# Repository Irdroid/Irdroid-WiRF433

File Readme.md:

#Irdroid WiRF433 - Single Board Linux Computer, Designed by Hardwate Group Ltd.
------------------------------------------------------------------------------
Irdroid WiRF433 is open source software and open source hardware, low cost starting
from USD 38 Linux Industrial grade single board computer with GPIOs capable to operate 
-25 - +85C

The Irdroid WiRF433 SBC is designed with the Ralink RT5350 SoC, 32Mbytes of RAM and 4 Mbytes of Flash.
The Irdroid WiRF433 board is designed with 2 ethernet ports, therefore the board can be 
used for routing. 

All the GPIOs of the RT5350 Soc are available on the WiRF433 board pin headers. The Irdroid WiRF433
comes also with a RF433MHZ RF module which allows for controlling IoT Remote control switches, light bulbs
and sockets operating at 433.9Mhz.

Irdroid WiRF433 is completely open source - including hardware and software, this means you have 
access to all CAD files and sources and you can reuse them for your own personal or commercial project.
There are NO restrictions to manufacture and sell these board for your own use or resale.

###Main Features:
- Mips Architecture CPU @360Mhz
- 32 Mbytes of SDRAM
- 4 Mbyets of FLASH memory
- 1 USB 2.0 HOST Port
- 1-SPI, 1-I2C , and on I2S (AUDIO)
- WiFi 802.11b/g/n interface
- 2 Ethernet interfaces 1WAN and 1LAN
- RF433 RF Remote control interface with onboard Antenna

The Irdroid WiRF433 SBC comes with preinstalled uboot bootloader and OpenWRT Linux distribution, which includes
also IoT remote control applications and software like RCSwitch for controlling RC 433.9Mhz remote control
switches and a Mobile HTML5 web application , configured for work with the RC switches, which gives the possibility to add unlimited number of RCSwitches

###APPLICATIONS:
- Home Automation Development Computer. The Open Source apps like LIRC,RCSwitch and serial web proxy will allow you to rapidly and easyly build Home Automation Systems
- IoT Development Computer. With its available interfaces, you can turn Irdroid WiRF433 into a IoT main unit, and you will be able to control RC Switches, RC Lights and RC Sockets
- Internet Router with IoT capabilities - The OpenWRT open source Linux distributions will allow you to easyly create one
- Inexpensive PLC with the open source protocols, available on the Internet.

###WEB RESOURCES:
- http://www.irdroid.com - The Irdroid project website, where Irdroid WiRF433 board info is hosted
- http://github.com/irdroid - Project's Github repositories.
- http://www.irdroid.eu/product/irdroid-wifi-rf433mhz-development-computer/ - Currently you can purchase a sample board from irdroid.eu for 38$

###HARDWARE
The Hardware project is released under the Creative Commons Attribution-Share Alike 3.0 United States License. You may reproduce it for both your own personal use, and for commertial use. You will have to provide a link to the original creator of the project http://www.irdroid.com on any documentation or website.
You may also modify the files, but you must then release them as well under the same terms.Credit can be attributed through a link to the creator website: http://www.irdroid.com

###SOFTWARE
The Irdroid WiRF433 Development board comes with preinstalled uboot bootloader and the OpenWRT Linux distribution. The board also comes with the following preinstalled applications:
- RCSwitch for controlling RF433Mhz remote control sockets, lights and switches
- Web Based HTML5 Interface for RCSwitch

The software is released under GPL.

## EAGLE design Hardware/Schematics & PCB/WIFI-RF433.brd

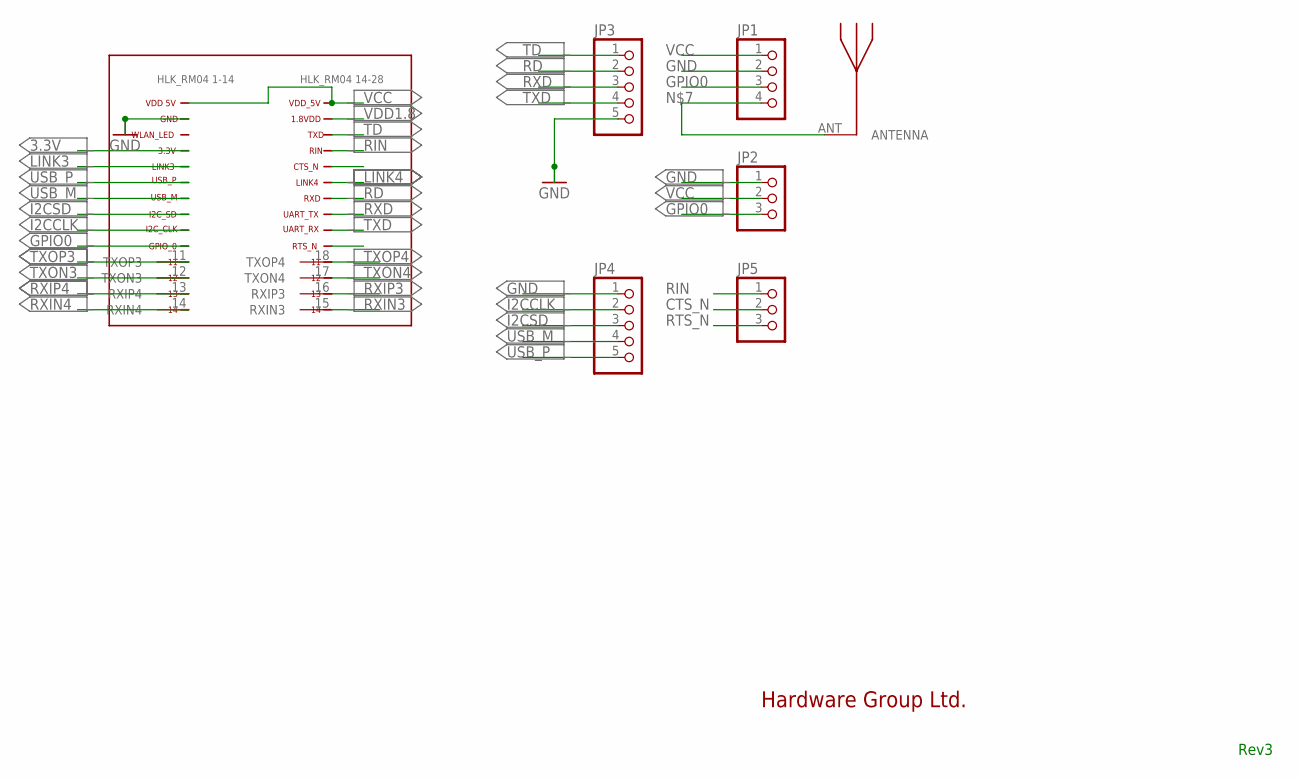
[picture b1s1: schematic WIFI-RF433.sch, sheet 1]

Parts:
JP1: PINHD-1X4; 1X04
JP2, JP5: PINHD-1X3; 1X03
JP3, JP4: PINHD-1X5; 1X05
U$4: 433MHZ
U$8: 1X10

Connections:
3.3V: U$8.4 (3.3VDD)
CTS_N: JP5.2, U$8.24 (CTS_N)
GND: JP1.2, JP2.1, JP3.5, JP4.1, U$8.2 (GND); also elsewhere on the board
GPIO0: JP1.3, JP2.3, U$8.10 (GPIO_0)
I2CCLK: JP4.2, U$8.9 (I2C_CLK)
I2CSD: JP4.3, U$8.8 (I2C_SD)
LINK3: U$8.5 (LINK3); also elsewhere on the board
LINK4: U$8.23 (LINK4); also elsewhere on the board
unnamed: JP1.4, U$4.ANT
RD: JP3.2, U$8.22 (RXD)
RIN: JP5.1, U$8.25 (RIN)
RTS_N: JP5.3, U$8.19 (RTS_N)
RXD: JP3.3, U$8.21 (UART_TX)
RXIN3: U$8.15 (RXIN3); also elsewhere on the board
RXIN4: U$8.14 (RXIN4); also elsewhere on the board
RXIP3: U$8.16 (RXIP3); also elsewhere on the board
RXIP4: U$8.13 (RXIP4); also elsewhere on the board
TD: JP3.1, U$8.26 (TXD)
TXD: JP3.4, U$8.20 (UART_RX)
TXON3: U$8.12 (TXON3); also elsewhere on the board
TXON4: U$8.17 (TXON4); also elsewhere on the board
TXOP3: U$8.11 (TXOP3); also elsewhere on the board
TXOP4: U$8.18 (TXOP4); also elsewhere on the board
USB_M: JP4.4, U$8.7 (USB_M)
USB_P: JP4.5, U$8.6 (USB_P)
VCC: JP1.1, JP2.2, U$8.1 (VDD_5V), U$8.28 (VDD_5V_); also elsewhere on the board
VDD1.8: U$8.27 (1.8VDD); also elsewhere on the board

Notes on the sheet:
Hardware Group Ltd.
Rev3

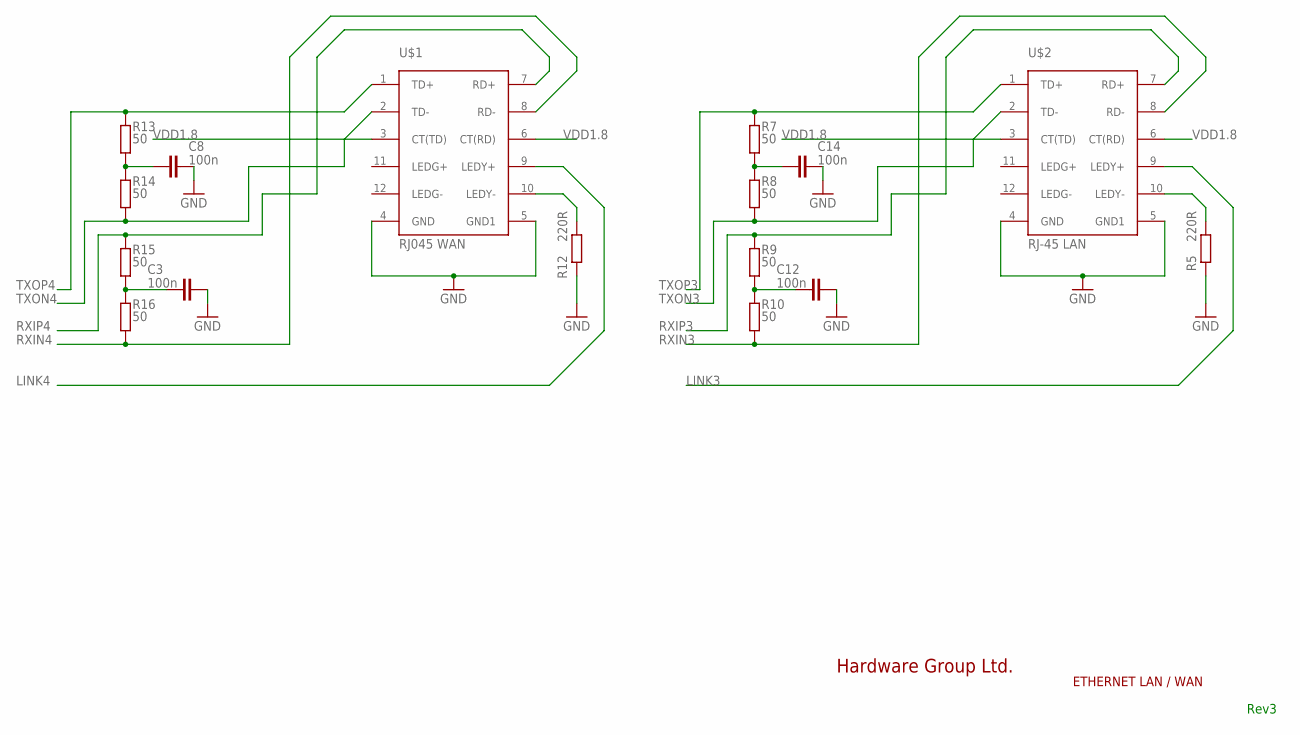
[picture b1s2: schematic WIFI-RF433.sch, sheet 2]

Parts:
C3, C8, C12, C14: 100n; C0805
R5, R12: 220R; R0805
R7, R8, R9, R10, R13, R14, R15, R16: 50; R0805
U$1: RJ045 WAN; MAGJACK
U$2: RJ-45 LAN; MAGJACK

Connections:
GND: C3.2, C8.2, C12.2, C14.2, R5.1, R12.1, U$1.4 (GND), U$1.5 (GND1), U$2.4 (GND), U$2.5 (GND1); also elsewhere on the board
LINK3: U$2.9 (LEDY+); also elsewhere on the board
LINK4: U$1.9 (LEDY+); also elsewhere on the board
unnamed: R5.2, U$2.10 (LEDY-)
unnamed: C3.1, R15.1, R16.2
unnamed: R12.2, U$1.10 (LEDY-)
unnamed: C8.1, R13.1, R14.2
unnamed: C14.1, R7.1, R8.2
unnamed: C12.1, R9.1, R10.2
RXIN3: R10.1, U$2.8 (RD-); also elsewhere on the board
RXIN4: R16.1, U$1.8 (RD-); also elsewhere on the board
RXIP3: R9.2, U$2.7 (RD+); also elsewhere on the board
RXIP4: R15.2, U$1.7 (RD+); also elsewhere on the board
TXON3: R8.1, U$2.2 (TD-); also elsewhere on the board
TXON4: R14.1, U$1.2 (TD-); also elsewhere on the board
TXOP3: R7.2, U$2.1 (TD+); also elsewhere on the board
TXOP4: R13.2, U$1.1 (TD+); also elsewhere on the board
VDD1.8: U$1.3 (CT(TD)), U$1.6 (CT(RD)), U$2.3 (CT(TD)), U$2.6 (CT(RD)); also elsewhere on the board

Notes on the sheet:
Hardware Group Ltd.
ETHERNET LAN / WAN
Rev3

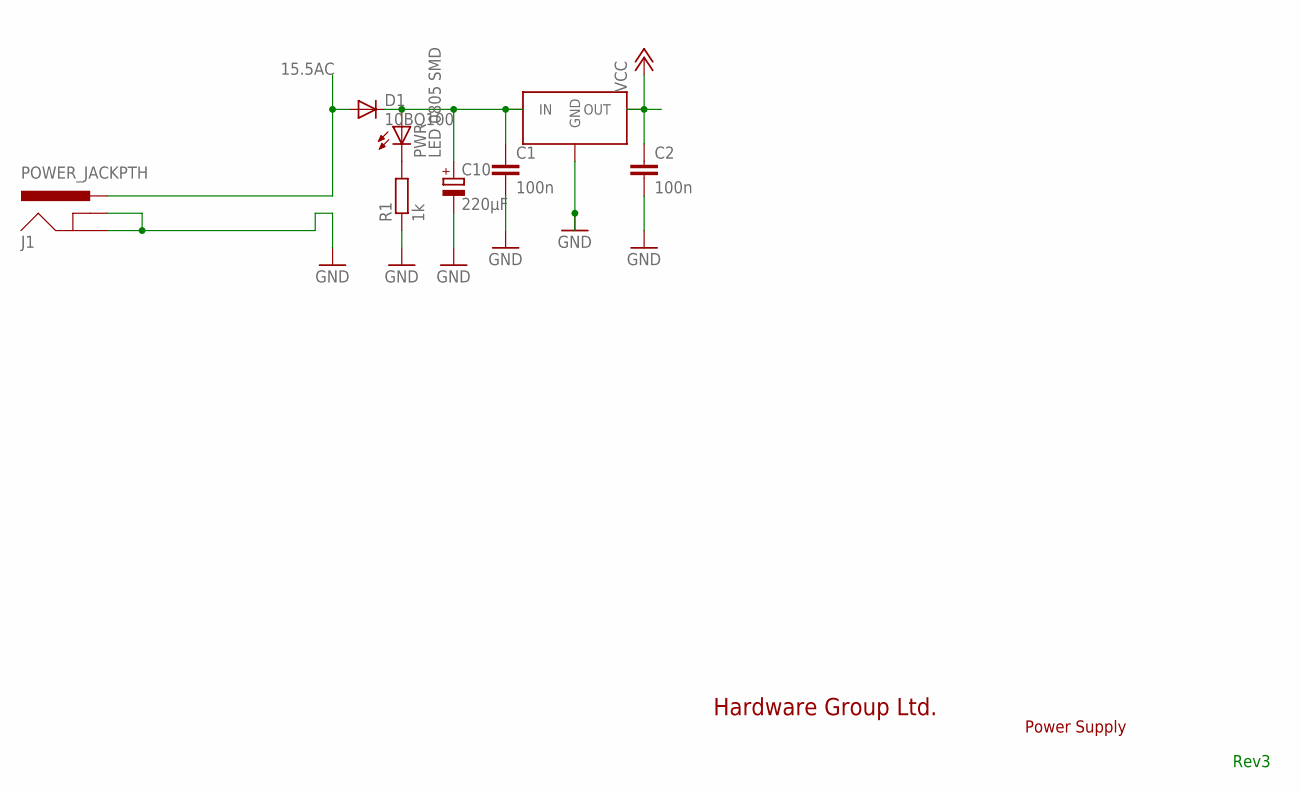
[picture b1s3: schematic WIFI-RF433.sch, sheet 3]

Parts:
C1, C2: 100n; C0805
C10: 220µF; E3,5-8
D1: 10BQ100; SMB
J1: POWER_JACKPTH; POWER_JACK_PTH
PWR: LED 0805 SMD; CHIP-LED0805
R1: 1k; M0805
U$3: VREG-7805-DPAK2

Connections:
15.5AC: D1.A, J1.PWR
GND: C1.2, C2.2, C10.-, J1.GND, J1.GNDBREAK, R1.1, U$3.GND; also elsewhere on the board
unnamed: PWR.C, R1.2
unnamed: C1.1, C10.+, D1.C, PWR.A, U$3.VIN (IN)
VCC: C2.1, U$3.VOUT (OUT); also elsewhere on the board

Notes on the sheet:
Hardware Group Ltd.
Power Supply
Rev3

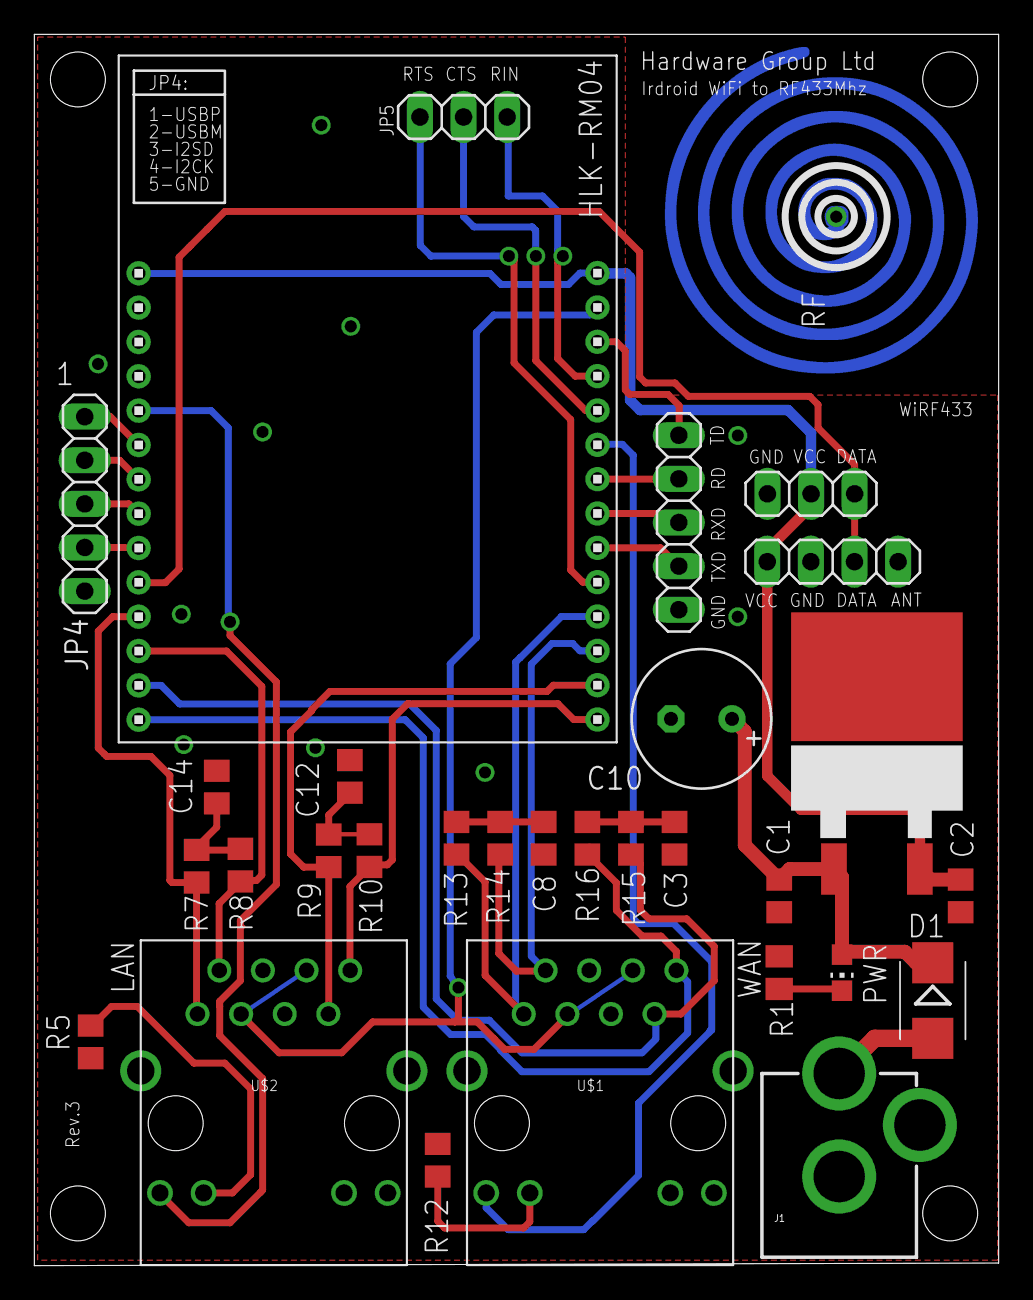
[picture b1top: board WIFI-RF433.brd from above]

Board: 2 copper layers, 56.2 x 71.7 mm, 31 parts (0 on the bottom side), 35 nets.

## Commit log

2015-04-20 :octocat: Added .gitattributes & .gitignore files
2015-04-21 Changed readme.md
2015-04-21 Second update of Readme.md

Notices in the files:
parts and their libraries:
SparkFun-Connectors: Licensing: Creative Commons ShareAlike 4.0 International - https://creativecommons.org/licenses/by-sa/4.0
